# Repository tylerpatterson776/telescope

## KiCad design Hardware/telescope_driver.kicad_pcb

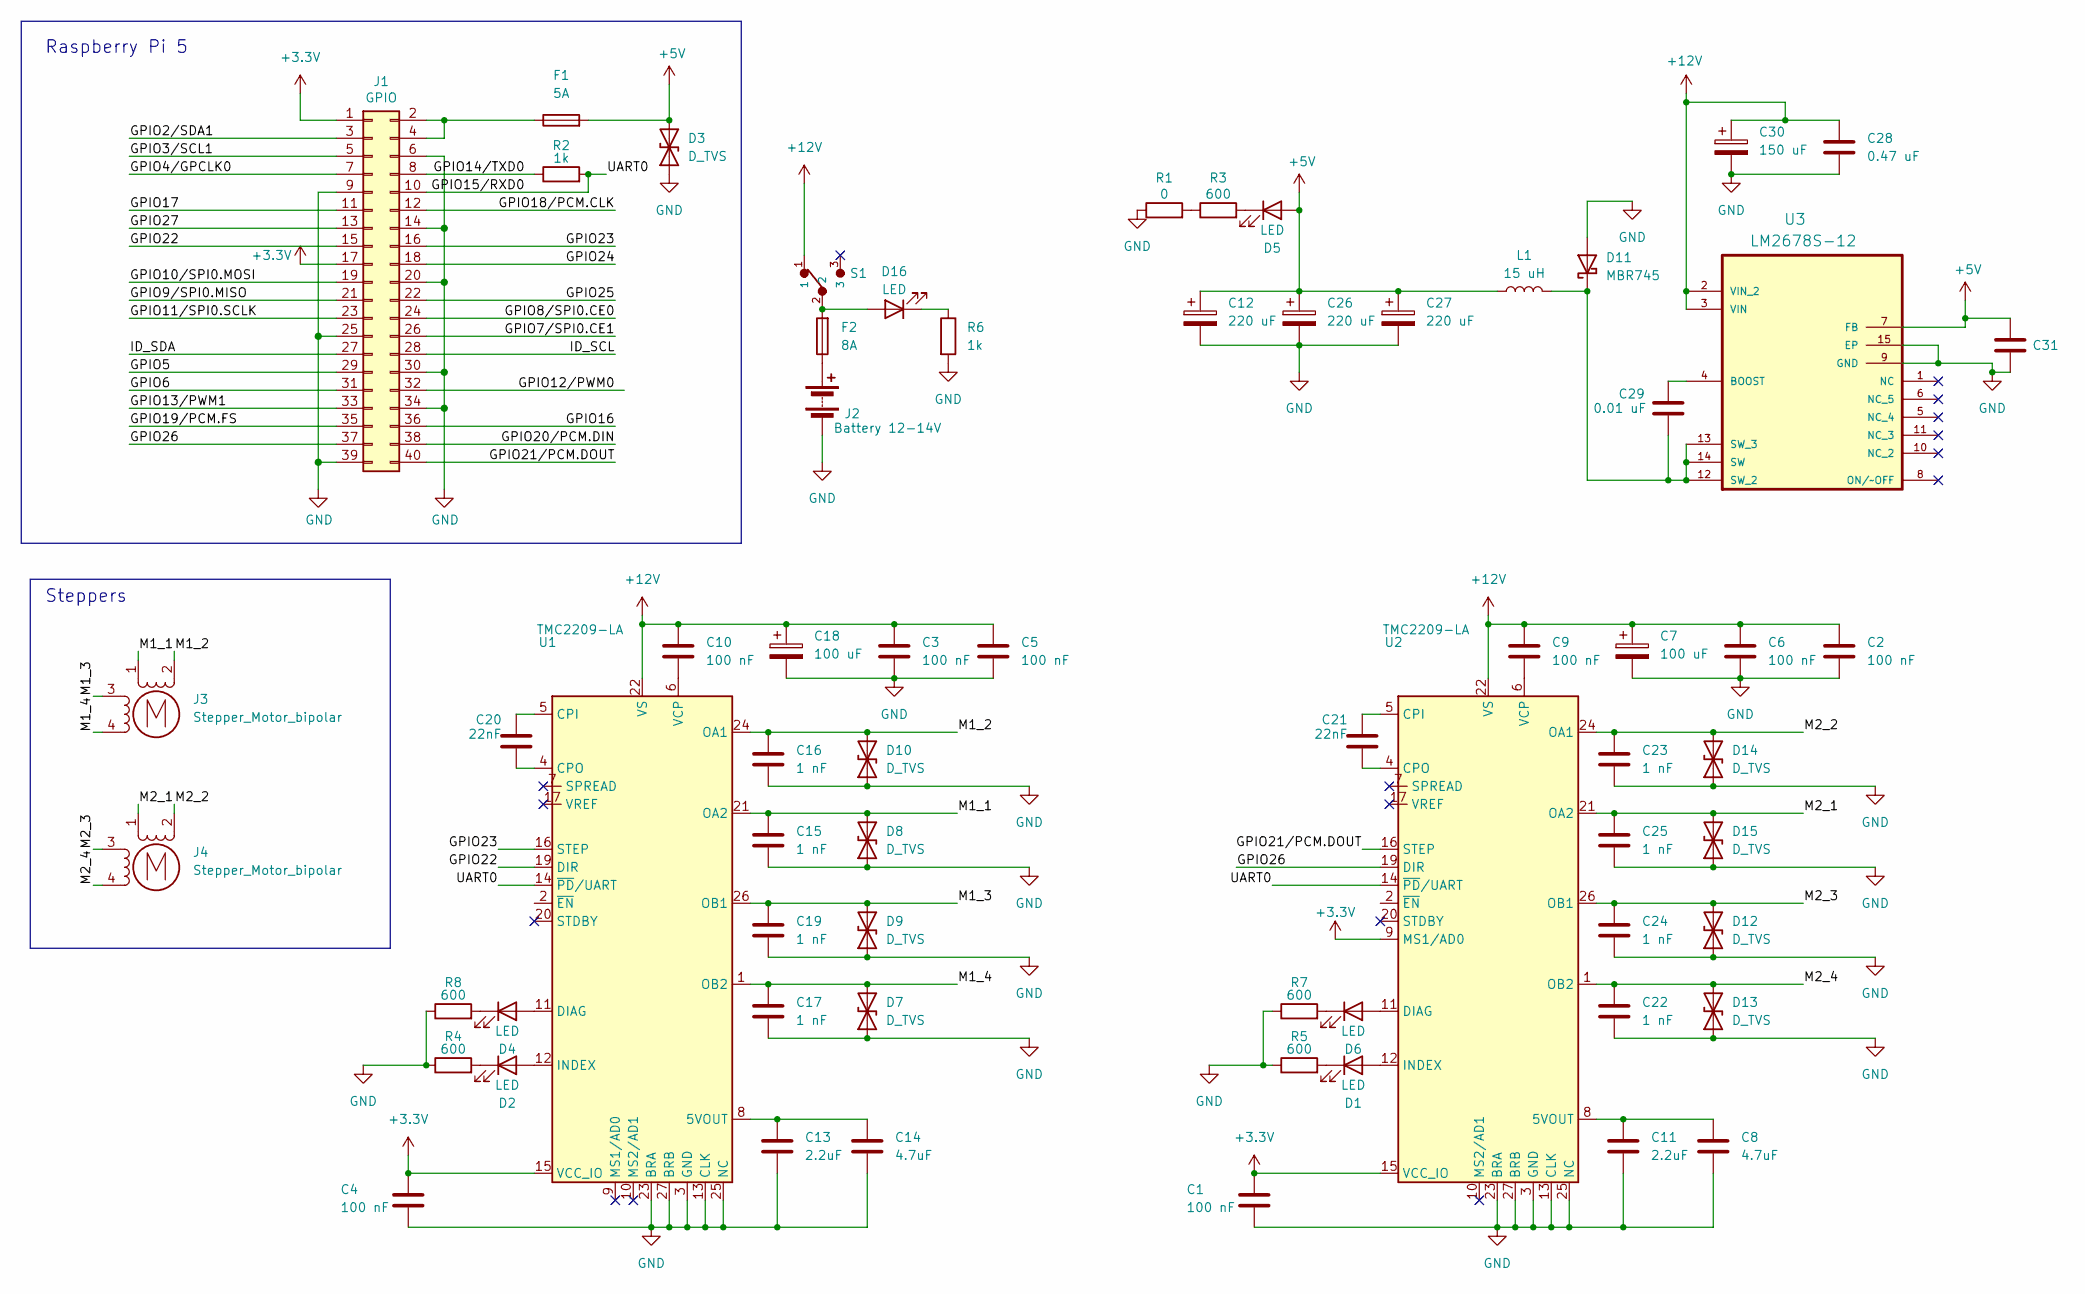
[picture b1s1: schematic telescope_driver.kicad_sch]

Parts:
C1, C2, C3, C4, C5, C6, C9, C10: 100 nF; C_1206_3216Metric_Pad1.33x1.80mm_HandSolder
C7, C18: 100 uF; C_ALUM_100UF_WCAP-ASLI_6.3X7.7_DXL_
C8, C14: 4.7uF; C_1206_3216Metric_Pad1.33x1.80mm_HandSolder
C11, C13: 2.2uF; C_1206_3216Metric_Pad1.33x1.80mm_HandSolder
C12, C26, C27: 220 uF; CP_EIA-7343-31_Kemet-D_HandSolder
C15, C16, C17, C19, C22, C23, C24, C25: 1 nF; C_0603_1608Metric_Pad1.08x0.95mm_HandSolder
C20, C21: 22nF; C_1206_3216Metric_Pad1.33x1.80mm_HandSolder
C28: 0.47 uF; C_1206_3216Metric_Pad1.33x1.80mm_HandSolder
C29, C31: 0.01 uF; C_0402_1005Metric_Pad0.74x0.62mm_HandSolder
C30: 150 uF; 20SVP150M
D1, D2, D4, D5, D6, D16: LED; LED_1206_3216Metric_Pad1.42x1.75mm_HandSolder
D3: D_TVS; D_TVS_SMB_STM
D7, D8, D9, D10, D12, D13, D14, D15: D_TVS; D_0201_0603Metric_Pad0.64x0.40mm_HandSolder
D11: MBR745; TO-220-2_Vertical
F1: 5A; FUSE_5A_0154005.DRL
F2: 8A; FUSE_5A_0154005.DRL
J1: GPIO; PinSocket_2x20_P2.54mm_Vertical
J2: Battery 12-14V; JST_B2PS-VH__LF__SN_
J3, J4: Stepper_Motor_bipolar; JST_PH_B4B-PH-K_1x04_P2.00mm_Vertical
L1: 15 uH; P0846NL
R1: 0; R_1206_3216Metric_Pad1.30x1.75mm_HandSolder
R2, R6: 1k; R_1206_3216Metric_Pad1.30x1.75mm_HandSolder
R3, R4, R5, R7, R8: 600; R_1206_3216Metric_Pad1.30x1.75mm_HandSolder
S1: 1101M2S3CQE2
U1: TMC2209-LA; VQFN-28-1EP_5x5mm_P0.5mm_EP3.7x3.7mm_ThermalVias
U2: TMC2209-LA; IC_DRIVER_TMC_2209_VQFN-28-1EP_5x5mm_P0.5mm_EP3.7x3.7mm_The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
U3: LM2678S-12; DFN500X600X100-15N; MPN LM2678SD-5.0

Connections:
+3.3V: C1.2, C4.2, J1.1, J1.17, U1.15 (VCC_IO), U2.9 (MS1/AD0), U2.15 (VCC_IO)
+5V: C12.1, C26.1, C27.1, C31.1, D3.2 (A2), D5.2 (A), F1.2, L1.1, U3.7 (FB)
+12V: C2.2, C3.2, C5.2, C6.2, C7.1, C9.2, C10.2, C18.1, C28.1, C30.1, S1.1, U1.22 (VS), U1.28 (VS), U2.22 (VS), U2.28 (VS), U3.2 (VIN_2), U3.3 (VIN)
/GPIO2/SDA1: J1.3
/GPIO3/SCL1: J1.5
/GPIO4/GPCLK0: J1.7
/GPIO5: J1.29
/GPIO6: J1.31
/GPIO7/SPI0.CE1: J1.26
/GPIO8/SPI0.CE0: J1.24
/GPIO9/SPI0.MISO: J1.21
/GPIO10/SPI0.MOSI: J1.19
/GPIO11/SPI0.SCLK: J1.23
/GPIO12/PWM0: J1.32
/GPIO13/PWM1: J1.33
/GPIO14/TXD0: J1.8, R2.1
/GPIO15/RXD0: J1.10, R2.2, U1.14 (~PD/UART), U2.14 (~PD/UART)
/GPIO16: J1.36
/GPIO17: J1.11
/GPIO18/PCM.CLK: J1.12
/GPIO19/PCM.FS: J1.35
/GPIO20/PCM.DIN: J1.38
/GPIO21/PCM.DOUT: J1.40, U2.16 (STEP)
/GPIO22: J1.15, U1.19 (DIR)
/GPIO23: J1.16, U1.16 (STEP)
/GPIO24: J1.18
/GPIO25: J1.22
/GPIO26: J1.37, U2.19 (DIR)
/GPIO27: J1.13
/ID_SCL: J1.28
/ID_SDA: J1.27
/M1_1: C15.2, D8.2 (A2), J3.1, U1.21 (OA2)
/M1_2: C16.2, D10.2 (A2), J3.2 (-), U1.24 (OA1)
/M1_3: C19.2, D9.2 (A2), J3.3, U1.26 (OB1)
/M1_4: C17.2, D7.2 (A2), J3.4, U1.1 (OB2)
/M2_1: C25.2, D15.2 (A2), J4.1, U2.21 (OA2)
/M2_2: C23.2, D14.2 (A2), J4.2 (-), U2.24 (OA1)
/M2_3: C24.2, D12.2 (A2), J4.3, U2.26 (OB1)
/M2_4: C22.2, D13.2 (A2), J4.4, U2.1 (OB2)
GND: C1.1, C2.1, C3.1, C4.1, C5.1, C6.1, C7.2, C8.2, C11.2, C12.2, C13.2, C14.2, C15.1, C16.1, C17.1, C18.2, C19.1, C22.1, C23.1, C24.1, C25.1, C26.2, C27.2, C28.2, C30.2, C31.2, D3.1 (A1), D7.1 (A1), D8.1 (A1), D9.1 (A1), D10.1 (A1), D11.2 (A), D12.1 (A1), D13.1 (A1), D14.1 (A1), D15.1 (A1), J1.6, J1.9, J1.14, J1.20, J1.25, J1.30, J1.34, J1.39, J2.2 (-), R1.1, R4.1, R5.1, R6.2, R7.1, R8.1, U1.3 (GND), U1.13 (CLK), U1.18 (GND), U1.23 (BRA), U1.25 (NC), U1.27 (BRB), U1.29 (GND), U2.3 (GND), U2.13 (CLK), U2.18 (GND), U2.23 (BRA), U2.25 (NC), U2.27 (BRB), U2.29 (GND), U3.9 (GND), U3.15 (EP)
unnamed: D1.2 (A), U2.12 (INDEX)
unnamed: D1.1 (K), R5.2
unnamed: D2.2 (A), U1.12 (INDEX)
unnamed: D2.1 (K), R4.2
unnamed: D4.2 (A), U1.11 (DIAG)
unnamed: D4.1 (K), R8.2
unnamed: D5.1 (K), R3.2
unnamed: D6.2 (A), U2.11 (DIAG)
unnamed: D6.1 (K), R7.2
unnamed: C29.2, D11.1 (K), L1.2, U3.12 (SW_2), U3.13 (SW_3), U3.14 (SW)
unnamed: D16.2 (A), F2.2, S1.2
unnamed: D16.1 (K), R6.1
unnamed: F1.1, J1.2, J1.4
unnamed: F2.1, J2.1 (+)
unnamed: R1.2, R3.1
unnamed: C13.1, C14.1, U1.8 (5VOUT)
unnamed: C20.1, U1.5 (CPI)
unnamed: C20.2, U1.4 (CPO)
unnamed: C10.1, U1.6 (VCP)
unnamed: C8.1, C11.1, U2.8 (5VOUT)
unnamed: C21.1, U2.5 (CPI)
unnamed: C21.2, U2.4 (CPO)
unnamed: C9.1, U2.6 (VCP)
unnamed: C29.1, U3.4 (BOOST)

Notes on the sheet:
Raspberry Pi 5
Steppers

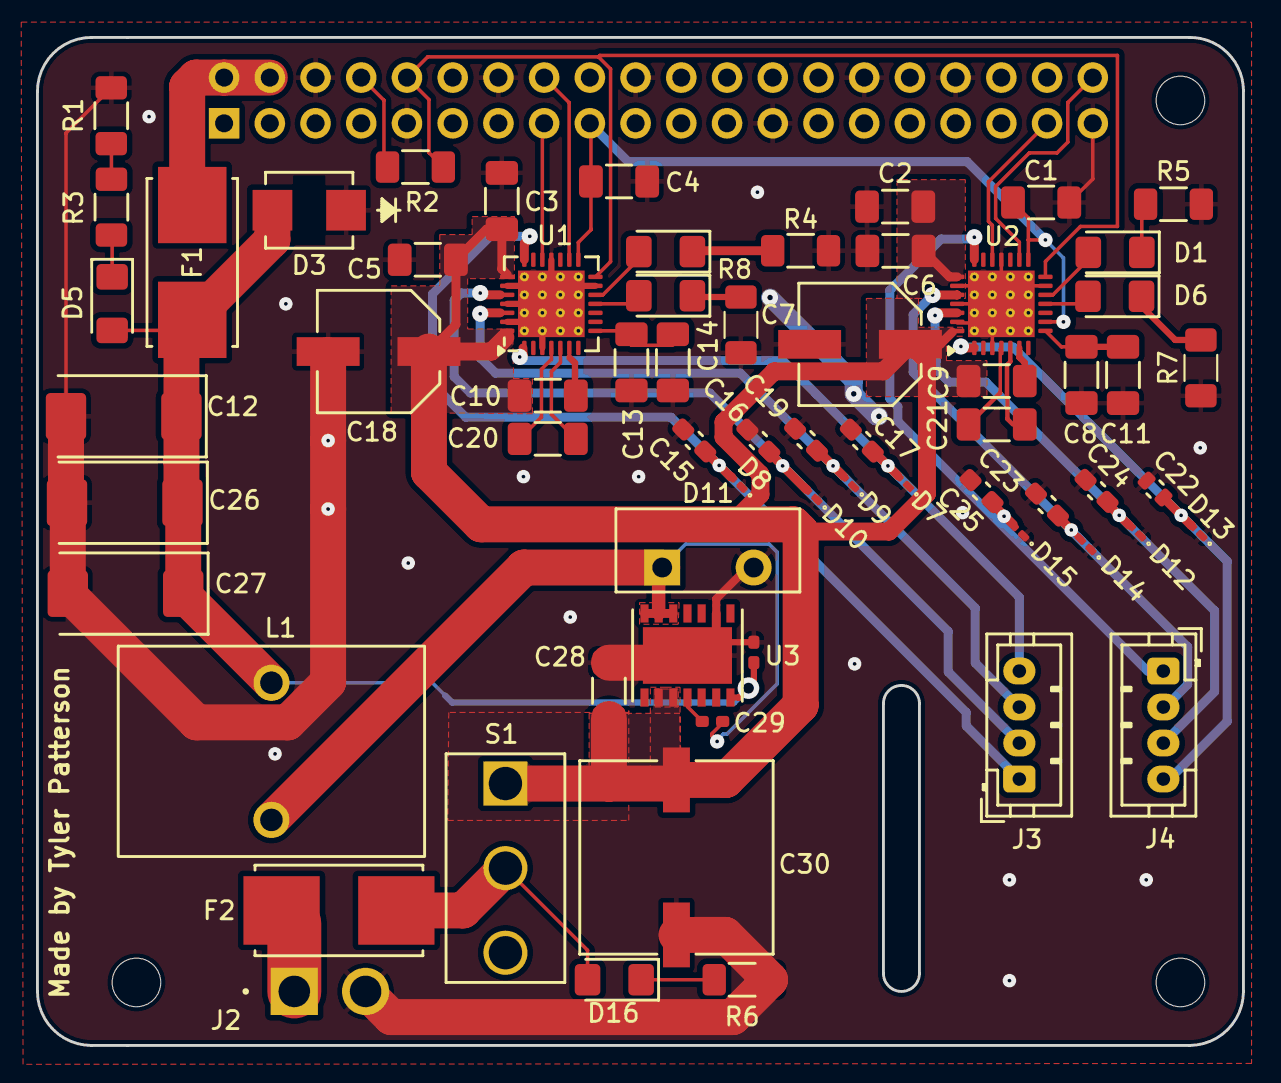
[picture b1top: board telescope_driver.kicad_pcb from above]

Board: 2 copper layers, 67.0 x 56.0 mm, 69 parts (1 on the bottom side), 42 nets.

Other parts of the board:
MH1, MH2, MH3: MountingHole_2.7mm_M2.5

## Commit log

2025-10-23 hello
2025-10-23 test
2025-10-23 parl
2025-10-23 finally
2025-10-24 some changes
2025-10-26 ready for production
2025-11-03 components ordered and some minor changes
